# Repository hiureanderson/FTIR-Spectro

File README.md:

# FTIR-Spectro

A DIY Infrared spectrometry project based on michelson interferometry and Fourrier transform analysis
The system relies on a Atmega32u4 MCU as its core and the code is developed using the abstracted Arduino environment.

## What is the current state ?

Last Update: 27.08.2016
The FTIR DIY spectrometer is currently in stanbye and needs students for the project to continue on.
The project is currently based at Octanis Assocation, in the Hackuarium Hackerspace in Renens, Switzerland.
More can be found on these organisations at:

  http://octanis.org   
  http://wiki.hackuarium.ch/w/Main_Page
  
## What needs to be done ?

* Change CAD so that material swelling due to water uptake is taken into account (or change Nylon for a more stable material)
* Retest the stability of the AC-DC network 96V rectifier down to mV oscillations
* Make a proper PCB board for the 96V rectifier with BOM and dedicated documentation and Specs
* Align the mirrors system with a laser
* Test the mirror displacement due to the piezo crystal with a laser and charaterize it
* Program the Atmega MCU to drive the DAC output and test this output voltage (it might be necessary to reorder a board)
* Couple the Atmega MCU to the 0-5V --> 0-96V converter and charaterize the output voltage
* Test the Control of the piezo dilatation with the Atmega and the 0-96V output you charaterized
* Determine if the sensor sensitivity is high enough, if not various options can be explored: change the amplifier resistor bridge, cool the sensor down to -50°C with a Peltier dedicated device to reduce SNR, test a PIR type of sensor, find a more suited sensor.
* Once this stage is complete determine how much light is lost passing in the PE liquid holding cell when empty and scan with the piezo to get the empty cell response (need to program a control loop on the MCU with sensor reading)
* Test the device with different liquids and perform fft on the data provided by the Atmega board to get spectra
* Charaterize for ammonia detection
* Provide a deliverable kit with user manual

Each step must be documented so no work is lost and the community can enjoy the results !!

## Contact

You can contact me concerning the project at quentin.cabrol@gmail.com.
We are currently searching for members to enroll and work on this project

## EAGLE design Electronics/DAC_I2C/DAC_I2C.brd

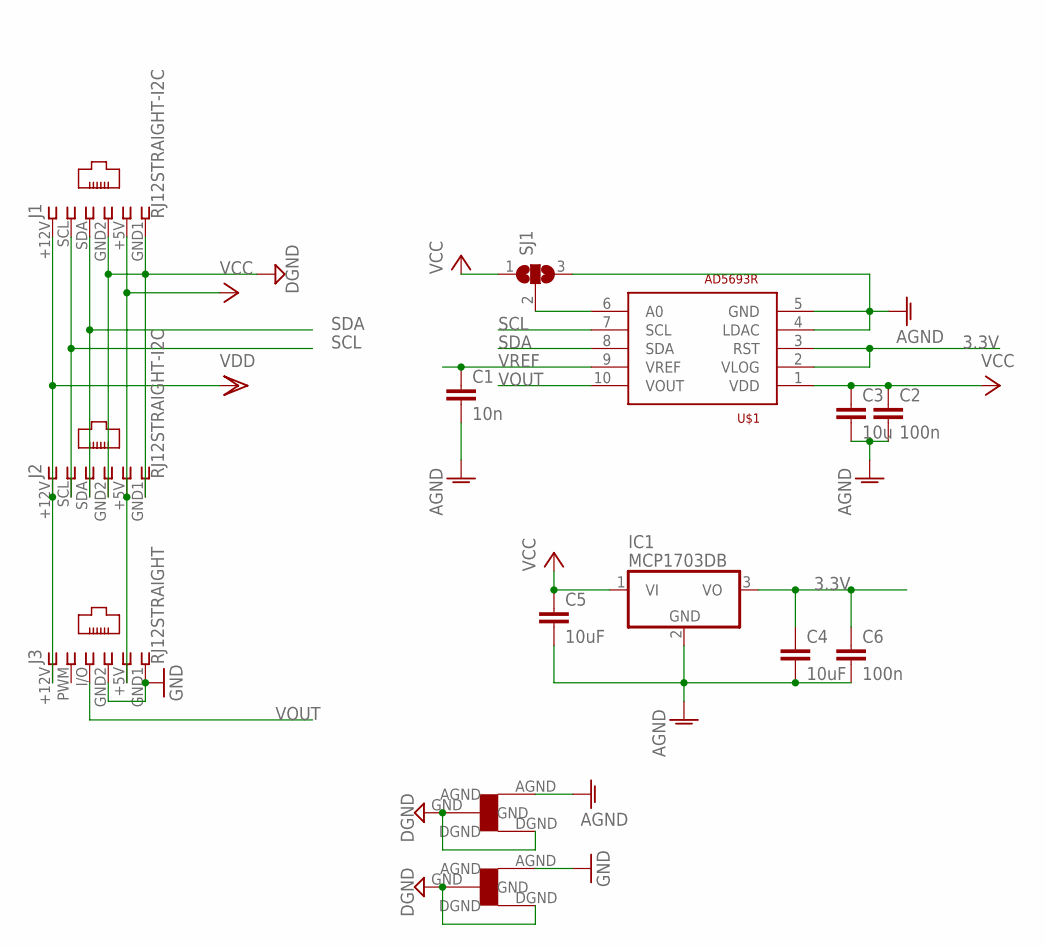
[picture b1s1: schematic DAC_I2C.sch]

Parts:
C1: 10n; C1206
C2, C6: 100n; C1206
C3: 10u; C1206
C4, C5: 10uF; C1206
IC1: MCP1703DB; SOT223
J1, J2: RJ12STRAIGHT-I2C; RJ12-STRAIGHT-I2C
J3: RJ12STRAIGHT; RJ12-STRAIGHT
SJ1: SJ2W; SJ_2
U$1: AD5693R; MSOP10
U$2, U$5: STARGND; STAR

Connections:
3.3V: C4.1, C6.1, IC1.3 (VO), U$1.2 (VLOG), U$1.3 (RST)
AGND: C1.2, C2.2, C3.2, C4.2, C5.2, C6.2, IC1.2 (GND), SJ1.3, U$1.4 (LDAC), U$1.5 (GND), U$5.AGND
DGND: J1.GND1 (6), J1.GND2 (4), J2.GND1 (6), J2.GND2 (4), U$2.DGND, U$2.GND, U$5.DGND, U$5.GND
GND: J3.GND1 (6), J3.GND2 (4), U$2.AGND
unnamed: SJ1.2, U$1.6 (A0)
SCL: J1.SCL (2), J2.SCL (2), U$1.7 (SCL)
SDA: J1.SDA (3), J2.SDA (3), U$1.8 (SDA)
VCC: C2.1, C3.1, C5.1, IC1.1 (VI), J1.+5V (5), J2.+5V (5), J3.+5V (5), SJ1.1, U$1.1 (VDD)
VDD: J1.+12V (1), J2.+12V (1), J3.+12V (1)
VOUT: J3.I/O (3), U$1.10 (VOUT)
VREF: C1.1, U$1.9 (VREF)

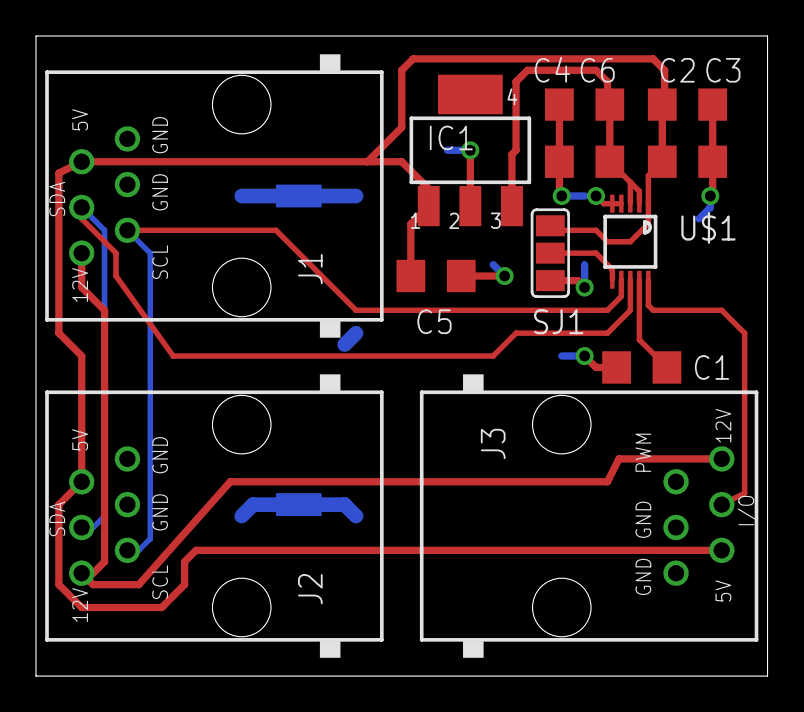
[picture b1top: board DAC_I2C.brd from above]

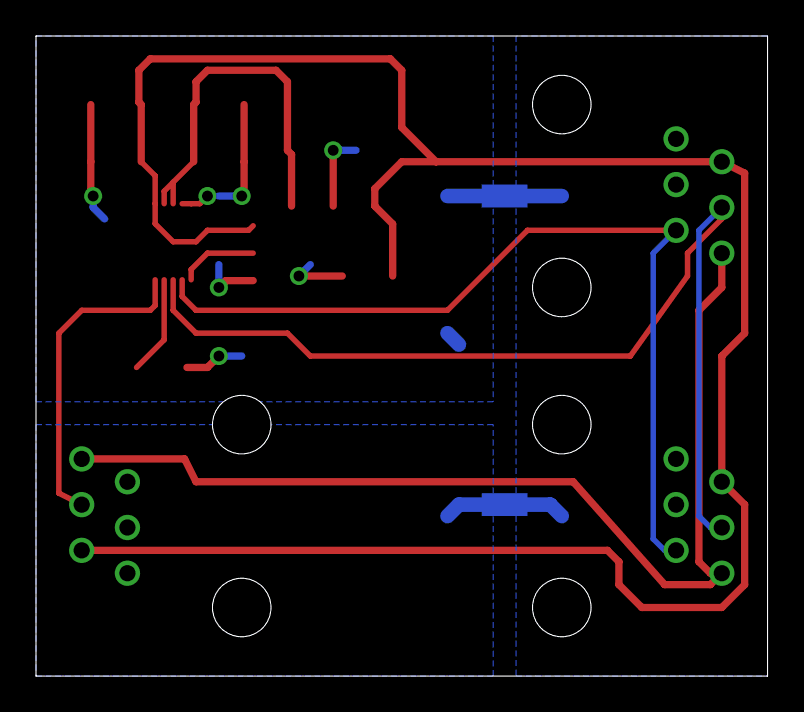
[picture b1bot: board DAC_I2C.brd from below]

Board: 2 copper layers, 40.6 x 35.6 mm, 14 parts (2 on the bottom side), 11 nets.

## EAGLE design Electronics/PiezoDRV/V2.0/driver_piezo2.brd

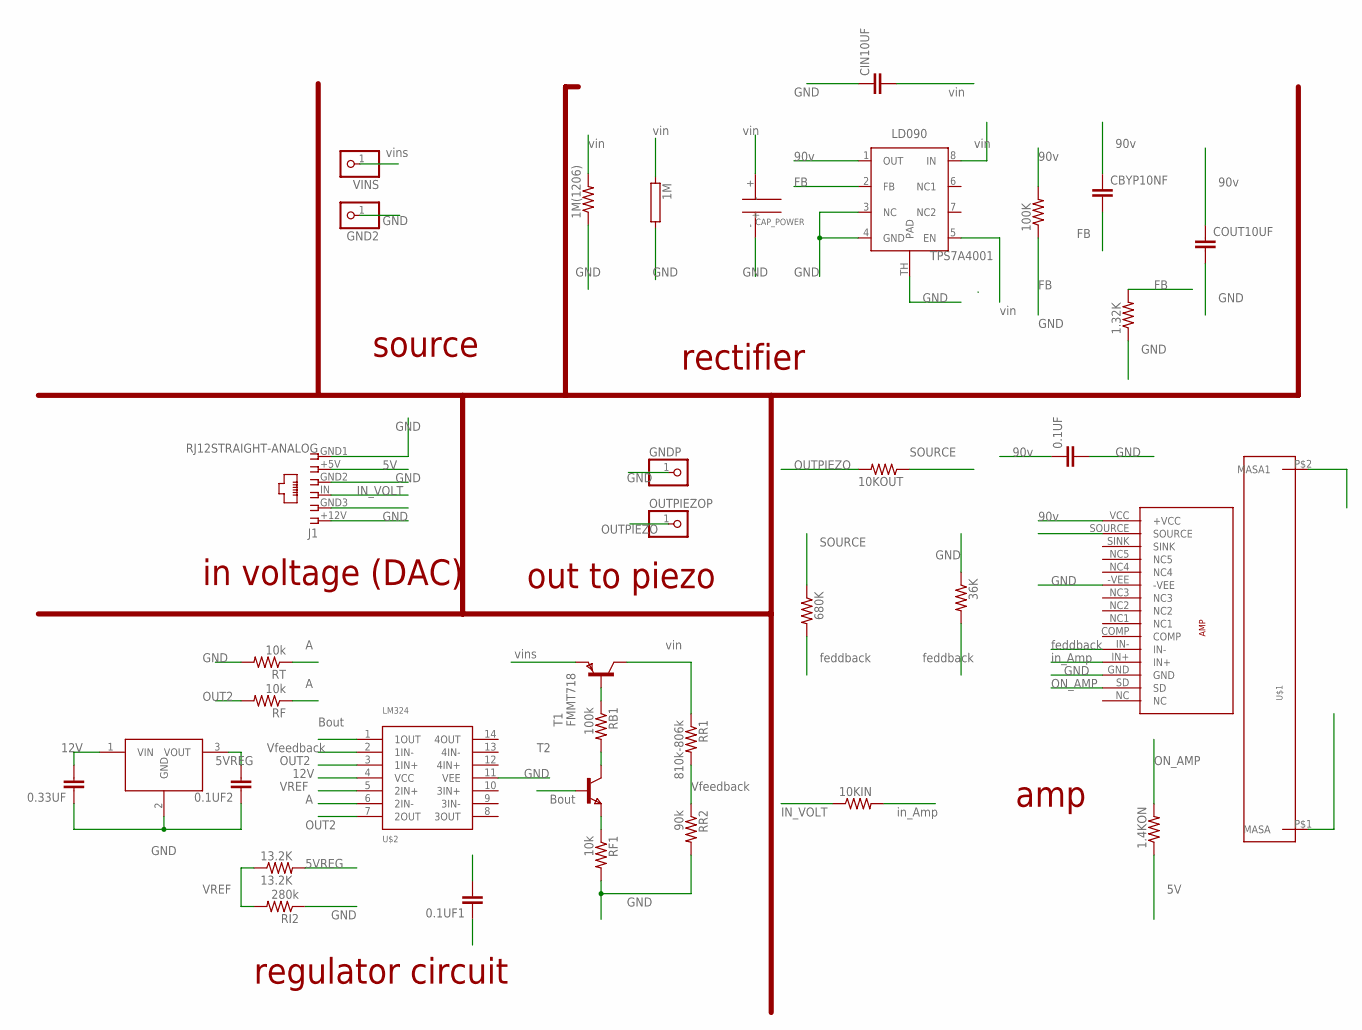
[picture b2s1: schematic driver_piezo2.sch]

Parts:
0.1UF, 0.1UF1, 0.1UF2, 0.33UF: C-EUC1206; C1206
1.4KON, 1.32K, 1M(1206), 10KIN, 10KOUT, 36K, 100K, 680K: R-US_R1206; R1206
1M: RCA0002; CA0002
13.2K: 13.2K; R1206
AMP: POWER_AMP_LME49811TB
CAP_POWER: CAP200VCAP200V; CAP200V
CBYP10NF: C-EUC1206; C1206
CIN10UF: C-EUC1206; C1206
COUT10UF: C-EUC1206; C1206
GND2: PINHD-1X1; 1X01
GNDP: PINHD-1X1; 1X01
J1: RJ12STRAIGHT-ANALOG; RJ12-STRAIGHT-ANALOG
LD090: TPS7A4001; S-PDSO-G08
OUTPIEZOP: PINHD-1X1; 1X01
RB1: 100k; R1206
RF, RF1: 10k; R1206
RI2: 280k; R1206
RR1: 810k-806k; R1206
RR2: 90k; R1206
RT: 10k; R1206
T1: FMMT718; SOT-23
T2: NPNSOT89; SOT89
U$1: DISIPADOR
U$2: LM324; SO14
U$3: 7805; TO220
VINS: PINHD-1X1; 1X01

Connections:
1OUT: T2.1 (B), U$2.1 (1OUT)
2IN+: 13.2K.1, RI2.2, U$2.5 (2IN+)
2IN-: RF.1, RT.1, U$2.6 (2IN-)
2OUT: RF.2, U$2.3 (1IN+), U$2.7 (2OUT)
5V: 1.4KON.1, J1.+5V (5)
5VOP: 0.1UF2.2, 13.2K.2, U$3.3 (VOUT)
12V: 0.1UF1.2, 0.33UF.2, J1.+12V (1), U$2.4 (VCC), U$3.1 (VIN)
B: 36K.2, 680K.2, AMP.IN-
FB: 1.32K.2, 100K.1, CBYP10NF.2, LD090.2 (FB)
GND: 0.1UF.2, 0.1UF1.1, 0.1UF2.1, 0.33UF.1, 1.32K.1, 1M.2, 1M(1206).1, 36K.1, AMP.-VEE, AMP.GND, CAP_POWER.-, CIN10UF.1, COUT10UF.2, GND2.1, GNDP.1, J1.GND1 (6), J1.GND2 (4), J1.GND3 (2), LD090.3 (NC), LD090.4 (GND), LD090.TH (PAD), RF1.2, RI2.1, RR2.2, RT.2, U$1.P$1 (MASA), U$1.P$2 (MASA1), U$2.11 (VEE), U$3.2 (GND)
IN_AMP: 10KIN.2, AMP.IN+
IN_VOLTAGE: 10KIN.1, J1.IN (3)
unnamed: RB1.2, T2.2 (C), T2.2@1 (C)
unnamed: RB1.1, T1.3 (B)
unnamed: RF1.1, T2.3 (E)
ON: 1.4KON.2, AMP.SD
OUT_PIEZO: 10KOUT.2, OUTPIEZOP.1
SOURCE: 10KOUT.1, 680K.1, AMP.SOURCE
V90: 0.1UF.1, 100K.2, AMP.VCC (+VCC), CBYP10NF.1, COUT10UF.1, LD090.1 (OUT)
VF: RR1.2, RR2.1, U$2.2 (1IN-)
VIN: 1M.1, 1M(1206).2, CAP_POWER.+, CIN10UF.2, LD090.5 (EN), LD090.8 (IN), RR1.1, T1.1 (C)
VINS: T1.2 (E), VINS.1

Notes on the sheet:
source
rectifier
out to piezo
amp
vins
vin
90v
GND
OUTPIEZO
IN_VOLT
ON_AMP
feddback
in voltage (DAC)
in_Amp
SOURCE
regulator circuit
Vfeedback
Bout
OUT2
12V
VREF
5VREG

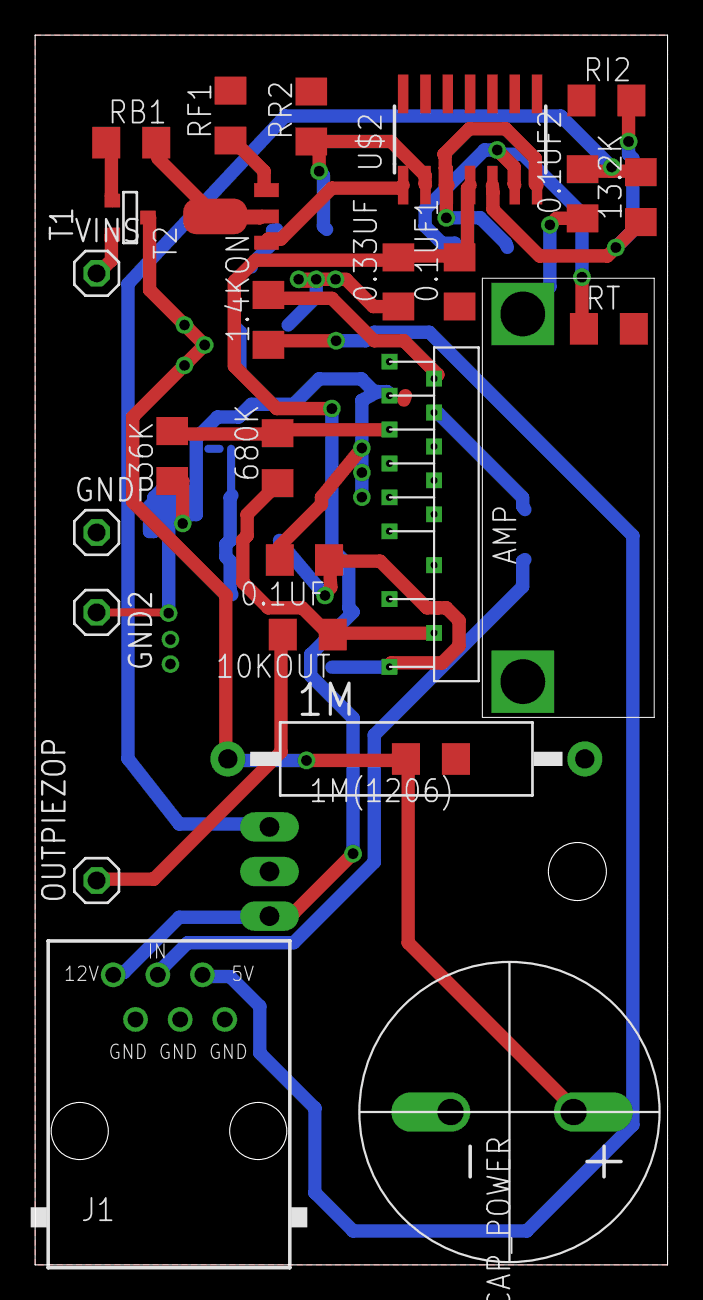
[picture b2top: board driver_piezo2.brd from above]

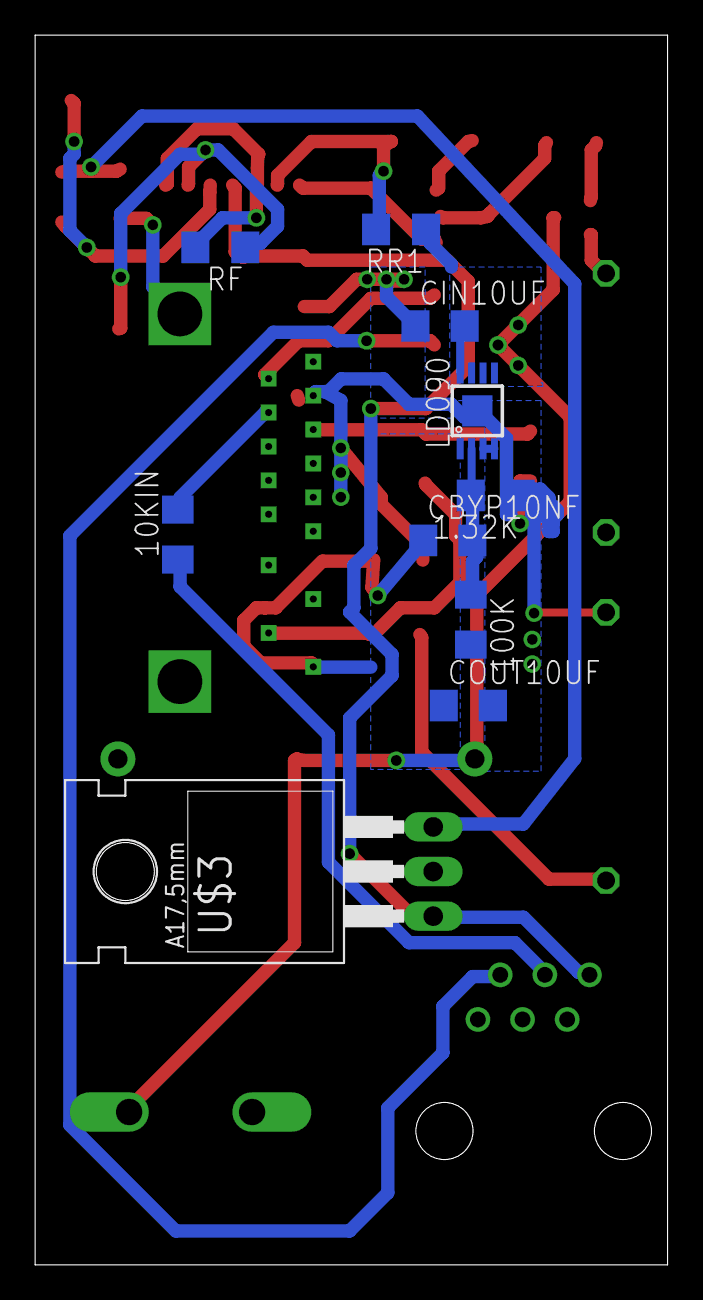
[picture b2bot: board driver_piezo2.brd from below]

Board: 2 copper layers, 36.0 x 70.0 mm, 37 parts (10 on the bottom side), 22 nets.

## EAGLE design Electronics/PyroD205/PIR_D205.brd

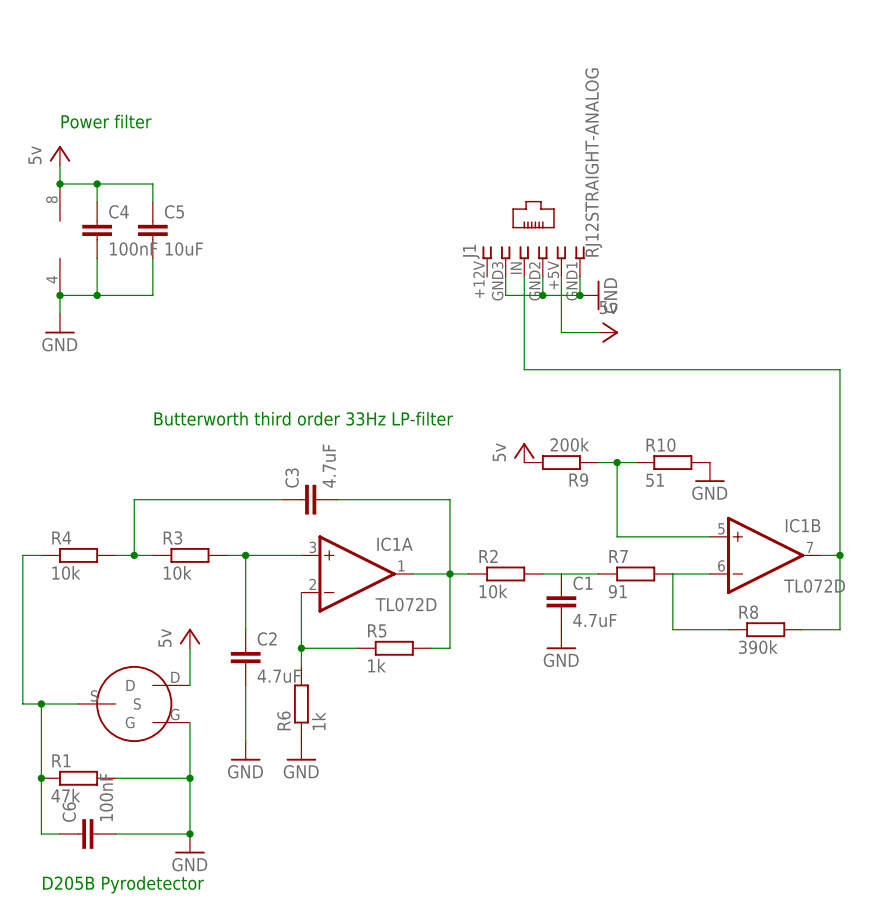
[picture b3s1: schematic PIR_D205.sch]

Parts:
C1, C2, C3: 4.7uF; C1206
C4, C6: 100nF; C1206
C5: 10uF; C1206
IC1: TL072D; SO08
J1: RJ12STRAIGHT-ANALOG; RJ12-STRAIGHT-ANALOG
R1: 47k; R1206
R2, R3, R4: 10k; R0805
R5, R6: 1k; R0805
R7: 91; R1206
R8: 390k; R1206
R9: 200k; R1206
R10: 51; R1206
U$1: D205B; TO5

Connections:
GND: C1.2, C2.2, C4.2, C5.2, C6.2, IC1.4 (V-), J1.GND1 (6), J1.GND2 (4), J1.GND3 (2), R1.2, R6.1, R10.2, U$1.G
unnamed: C6.1, R1.1, R4.1, U$1.S
unnamed: C3.2, IC1.1 (OUT), R2.1, R5.2
unnamed: IC1.2 (-IN), R5.1, R6.2
unnamed: C1.1, R2.2, R7.1
unnamed: C2.1, IC1.3 (+IN), R3.2
unnamed: C3.1, R3.1, R4.2
unnamed: IC1.6 (-IN), R7.2, R8.1
unnamed: IC1.7 (OUT), J1.IN (3), R8.2
unnamed: IC1.5 (+IN), R9.1, R10.1
VCC: C4.1, C5.1, IC1.8 (V+), J1.+5V (5), R9.2, U$1.D

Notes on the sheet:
Butterworth third order 33Hz LP-filter
D205B Pyrodetector
Power filter

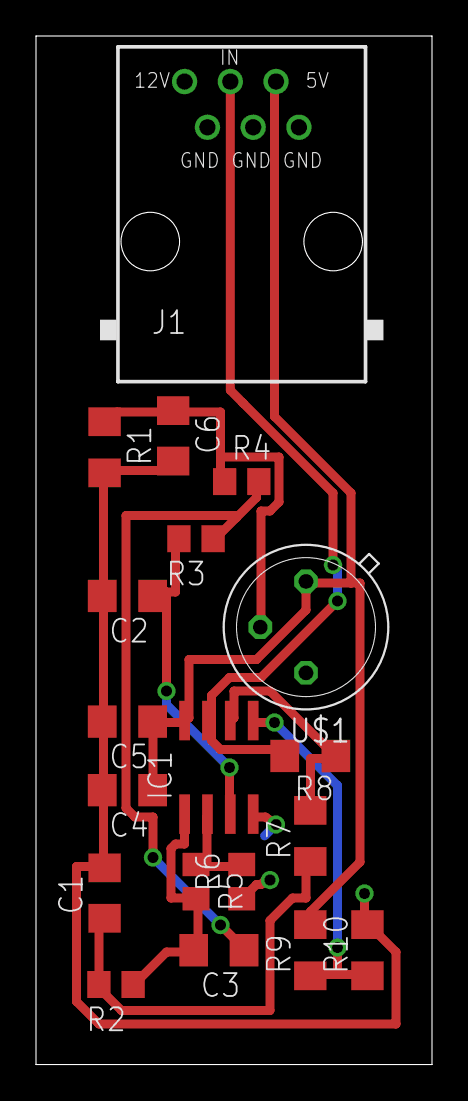
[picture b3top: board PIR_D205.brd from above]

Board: 2 copper layers, 22.0 x 57.1 mm, 19 parts (0 on the bottom side), 11 nets.

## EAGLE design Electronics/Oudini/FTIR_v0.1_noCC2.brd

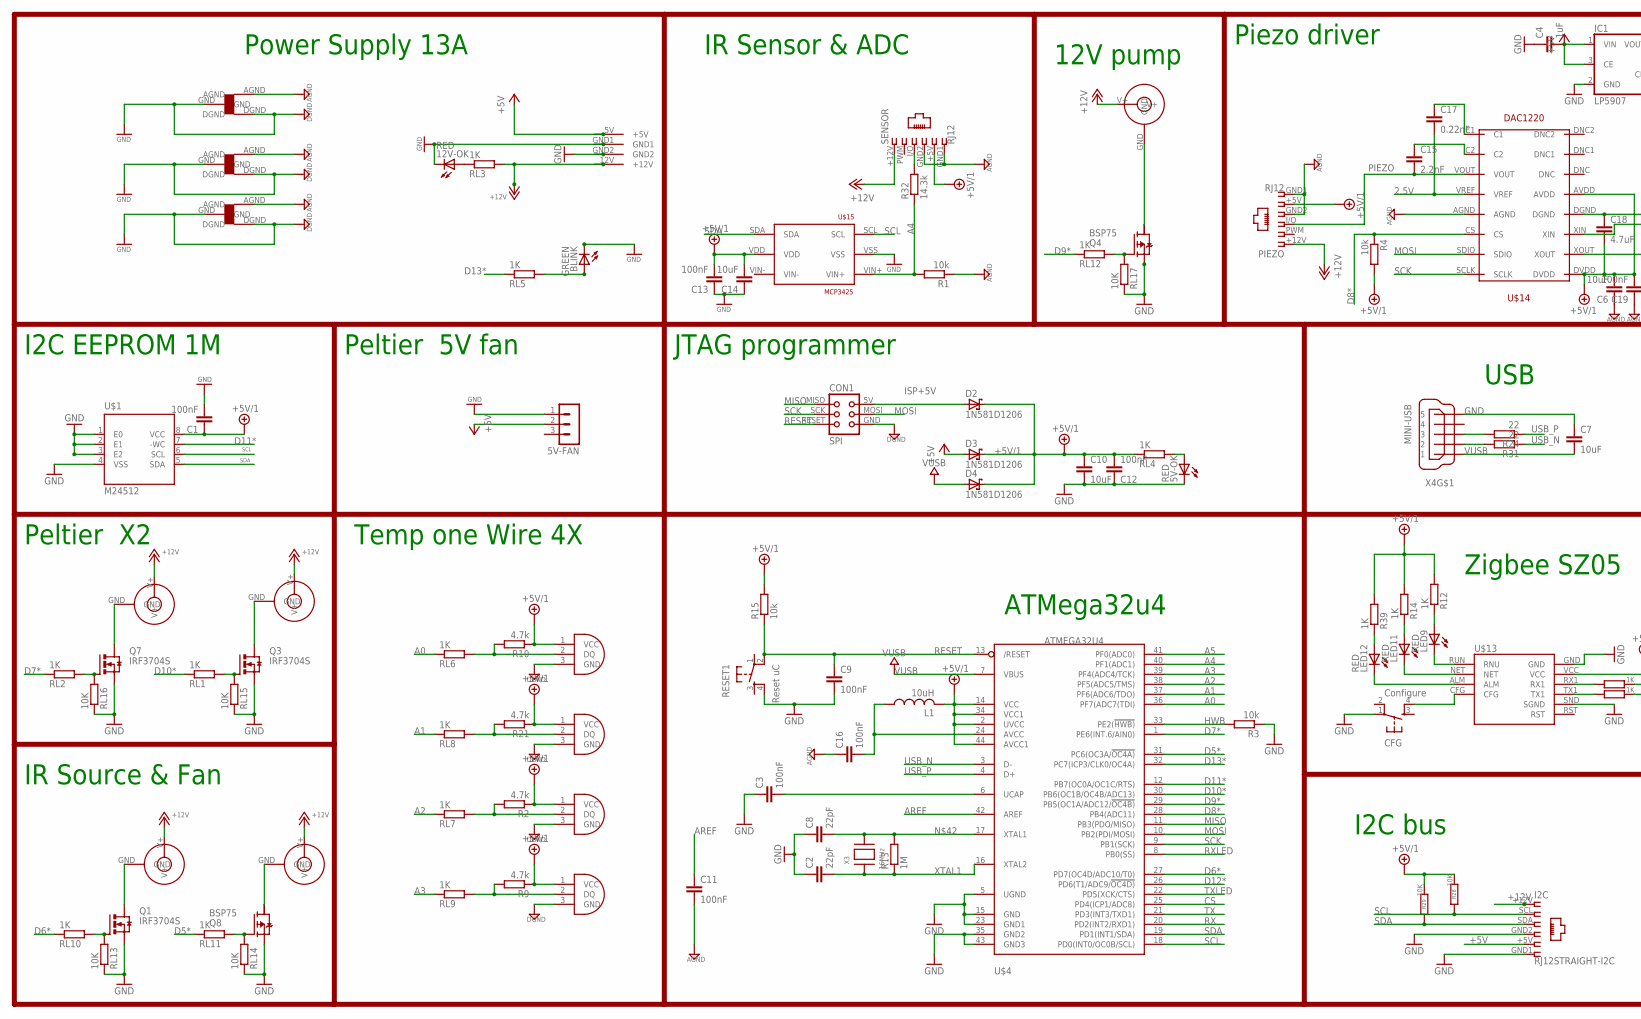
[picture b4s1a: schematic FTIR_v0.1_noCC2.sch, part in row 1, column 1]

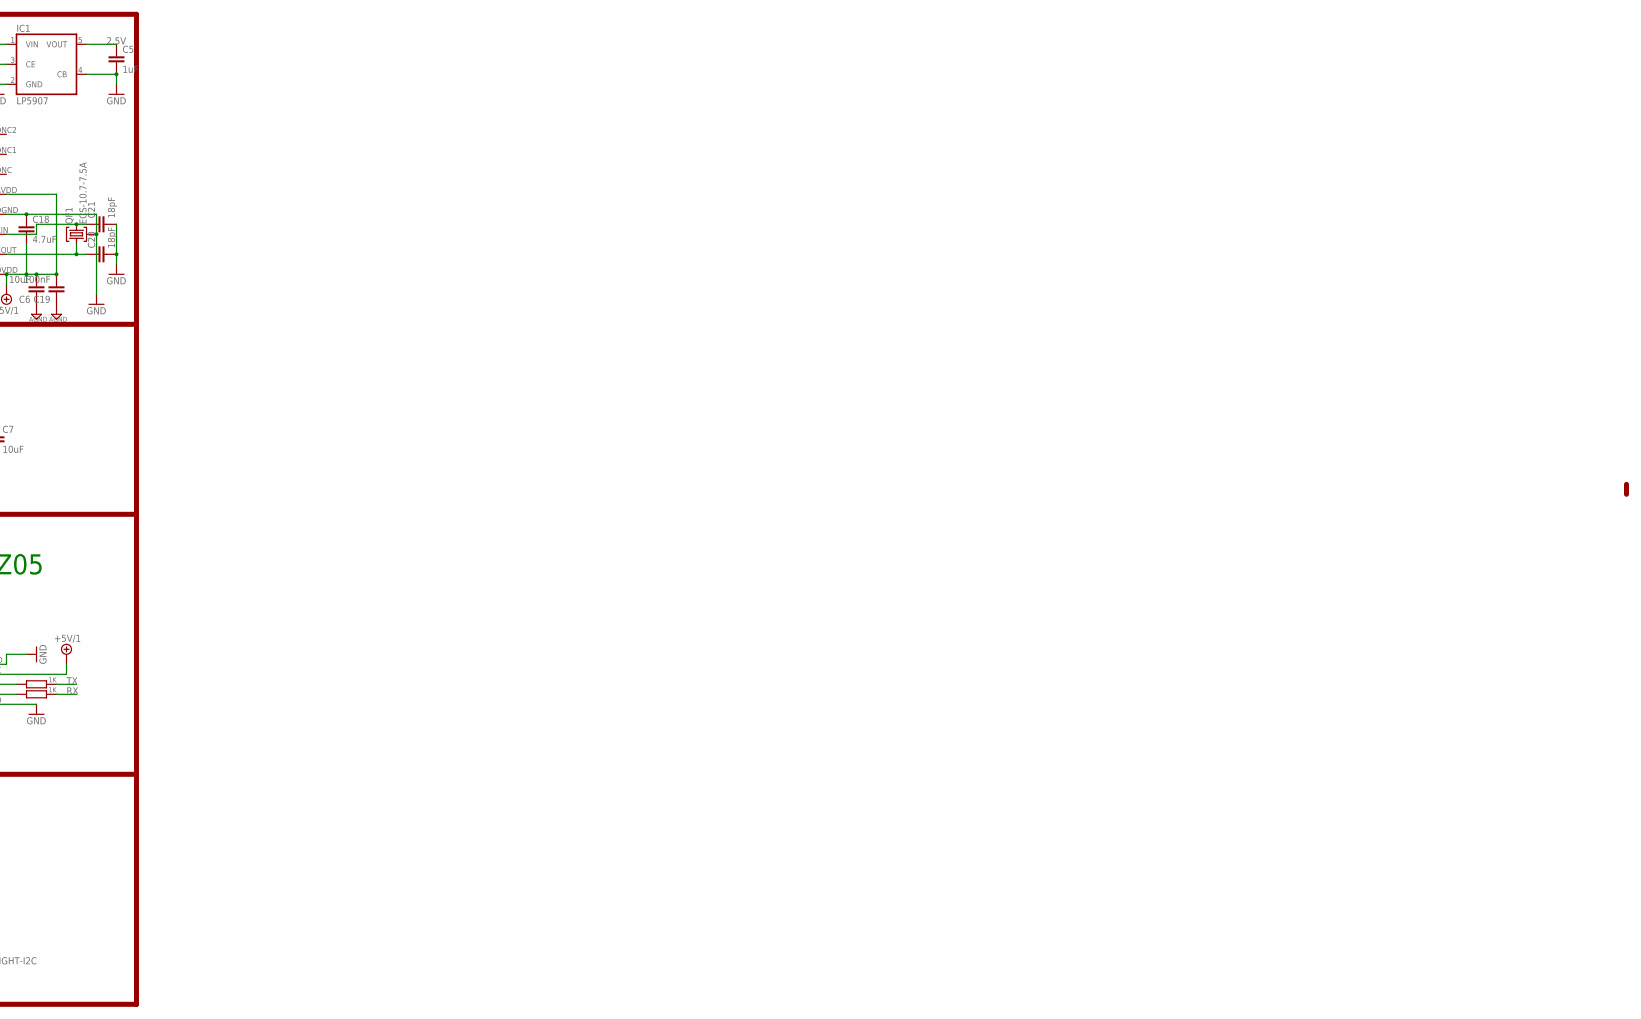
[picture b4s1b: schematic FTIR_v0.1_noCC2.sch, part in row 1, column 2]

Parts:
5V-FAN: MA03-1
5V-OK, 12V-OK: RED; CHIPLED_1206
BLINK: GREEN; CHIPLED_1206
C1, C3, C9, C11, C12, C13, C16, C19: 100nF; C1206
C2, C8: 22pF; C1206
C4, C5: 1uF; C1206
C6, C7, C10, C14: 10uF; C1206
C15: 2.2nF; C1206
C17: 0.22nF; C1206
C18: 4.7uF; C1206
C20, C21: 18pF; C1206
CFG: Configure; TACTILE_SWITCH_SMD
CON1: SPI; TC2030-MCP-NL
D2, D3, D4: 1N581D1206; LED-1206
I2C: RJ12STRAIGHT-I2C; RJ12-STRAIGHT-I2C
IC1: LP5907; SOT25
L1: 10uH; L2012C
LED9, LED11, LED12: RED; CHIPLED_1206
PIEZO: RJ12; RJ12-STRAIGHT
Q1, Q3, Q7: IRF3704S; D2PACK
Q4, Q8: BSP75; PG-SOT-223
QF1: ECS-10.7-7.5A; HC49U
R1, R4: 10k; R0805
R2, R9, R10, R21: 4.7k; R1206
R3, R15: 10k; M0805
R8, R11, R12, R14, R39: 1K; R0805
R13: 1M; R1206
R24, R31: 22; M1206
R28, R29: 10K; M0805
R32: 14.3k; R0805
RESET1: Reset uC; TACTILE_SWITCH_SMD
RL1, RL2, RL3, RL4, RL5, RL6, RL7, RL8, RL9, RL10, RL11, RL12: 1K; R0805
RL13, RL14, RL15, RL16, RL17: 10K; R0805
SENSOR: RJ12; RJ12-STRAIGHT
U$1: M24512; SO8
U$2, U$5, U$20: STARGND; STAR
U$3: AMP_MATE_N_LOCK
U$4: ATMEGA32U4; TQFP44
U$6, U$16, U$17, U$18, U$19: JACK_PJ-063BH; PJ-063BH
U$9, U$10, U$11, U$12: DS18B20_PINS; 3PINS_SMALL
U$13: SZ05-ZIGBEESMD; SZ05-ZIGBEE3
U$14: DAC1220; SSOP-16
U$15: MCP3425; SOT-23-6
X3: 16MHz; NX6035
X4: MINI-USB; 32005-201

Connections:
2.5V: C5.1, C17.2, IC1.5 (VOUT), U$14.VREF
+5V: 5V-FAN.2, C4.2, D3.A, I2C.+5V (5), IC1.1 (VIN), IC1.3 (CE), U$3.5V (+5V)
+5V/1: C1.1, C6.2, C10.1, C12.2, C13.2, C14.2, C18.2, C19.2, D2.C, D3.C, D4.C, L1.2, PIEZO.+5V (5), R2.1, R4.2, R9.1, R10.1, R12.2, R14.2, R15.2, R21.1, R28.1, R29.1, R39.2, RL4.1, SENSOR.+5V (5), U$1.8 (VCC), U$4.2 (UVCC), U$4.14 (VCC), U$4.34 (VCC1), U$4.44 (AVCC1), U$9.1 (VCC), U$10.1 (VCC), U$11.1 (VCC), U$12.1 (VCC), U$13.VCC, U$14.AVDD, U$14.DVDD, U$15.VDD
+12V: I2C.+12V (1), PIEZO.+12V (1), RL3.2, SENSOR.+12V (1), U$3.12V (+12V), U$6.V+, U$16.V+, U$17.V+, U$18.V+, U$19.V+
A0: RL6.1, U$4.36 (PF7(ADC7(TDI))
A1: RL8.1, U$4.37 (PF6(ADC6/TDO))
A2: RL7.1, U$4.38 (PF5(ADC5/TMS))
A3: RL9.1, U$4.39 (PF4(ADC4/TCK))
A4: R1.2, R32.1, U$4.40 (PF1(ADC1)), U$15.VIN+
A5: U$4.41 (PF0(ADC0))
AGND: C6.1, C11.2, C16.1, C19.1, PIEZO.GND1 (6), PIEZO.GND2 (4), R1.1, SENSOR.GND1 (6), SENSOR.GND2 (4), U$2.AGND, U$5.AGND, U$14.AGND, U$20.AGND
AREF: C11.1, U$4.42 (AREF)
CS: U$4.25 (PD4(ICP1/ADC8))
D5*: RL11.1, U$4.31 (PC6(OC3A/!OC4A))
D6*: RL10.1, U$4.27 (PD7(OC4D/ADC10/T0))
D7*: RL2.1, U$4.1 (PE6(INT.6/AIN0))
D8*: R4.1, U$4.28 (PB4(ADC11)), U$14.CS
D9*: RL12.1, U$4.29 (PB5(OC1A/ADC12/!OC4B))
D10*: RL1.1, U$4.30 (PB6(OC1B/OC4B/ADC13))
D11*: U$1.7 (-WC), U$4.12 (PB7(OC0A/OC1C/RTS))
D12*: U$4.26 (PD6(T1/ADC9/!OC4D))
D13*: RL5.1, U$4.32 (PC7(ICP3/CLK0/OC4A))
GND: 5V-FAN.1, 5V-OK.C, 12V-OK.C, BLINK.C, C1.2, C2.1, C3.1, C4.1, C5.2, C7.1, C8.1, C9.2, C10.2, C12.1, C13.1, C14.1, C18.1, C20.2, C21.2, CFG.1, CON1.GND, I2C.GND1 (6), I2C.GND2 (4), IC1.2 (GND), IC1.4 (CB), Q1.3 (S), Q3.3 (S), Q4.3 (S), Q7.3 (S), Q8.3 (S), QF1.2, R3.1, RESET1.4, RL13.1, RL14.1, RL15.1, RL16.1, RL17.1, U$1.1 (E0), U$1.2 (E1), U$1.3 (E2), U$1.4 (VSS), U$2.DGND, U$2.GND, U$3.GND1, U$3.GND2, U$4.5 (UGND), U$4.15 (GND), U$4.23 (GND1), U$4.35 (GND2), U$4.43 (GND3), U$5.DGND, U$5.GND, U$9.3 (GND), U$10.3 (GND), U$11.3 (GND), U$12.3 (GND), U$13.GND, U$13.SND (SGND), U$14.DGND, U$15.VSS, U$20.DGND, U$20.GND, X4.5
GND1: LED9.C, U$13.RUN (RNU)
GND2: LED11.C, U$13.NET
GND3: LED12.C, U$13.ALM
HWB: R3.2, U$4.33 (PE2(!HWB))
ISP+5V: CON1.5V (VCC), D2.A
MISO: CON1.MISO, U$4.11 (PB3(PDO/MISO))
MOSI: CON1.MOSI, U$4.10 (PB2(PDI/MOSI)), U$14.SDIO
unnamed: Q4.1 (G), RL12.2, RL17.2
unnamed: R32.2, SENSOR.I/O (3)
unnamed: BLINK.A, RL5.2
unnamed: Q4.2 (D), U$19.GND
unnamed: Q7.1 (G), RL2.2, RL16.2
unnamed: Q1.2 (D), U$17.GND
unnamed: R21.2, RL8.2, U$10.2 (DQ)
unnamed: R11.2, U$13.RX1
unnamed: 5V-OK.A, RL4.2
unnamed: Q3.1 (G), RL1.2, RL15.2
unnamed: C16.2, L1.1, U$4.24 (AVCC)
unnamed: C15.1, U$14.C2
unnamed: C3.2, U$4.6 (UCAP)
unnamed: R2.2, RL7.2, U$11.2 (DQ)
unnamed: R9.2, RL9.2, U$12.2 (DQ)
unnamed: C21.1, QF1.3, U$14.XIN
unnamed: R10.2, RL6.2, U$9.2 (DQ)
unnamed: Q8.2 (D), U$18.GND
unnamed: R8.2, U$13.TX1
unnamed: LED9.A, R12.1
unnamed: LED11.A, R14.1
unnamed: LED12.A, R39.1
unnamed: Q1.1 (G), RL10.2, RL13.2
unnamed: C17.1, U$14.C1
unnamed: Q7.2 (D), U$6.GND
unnamed: C20.1, QF1.1, U$14.XOUT
unnamed: Q3.2 (D), U$16.GND
unnamed: CFG.4, U$13.CFG
unnamed: Q8.1 (G), RL11.2, RL14.2
unnamed: C8.2, R13.2, U$4.17 (XTAL1), X3.P$2
unnamed: 12V-OK.A, RL3.1
PIEZO: C15.2, PIEZO.I/O (3), U$14.VOUT
RESET: C9.1, CON1.RESET, R15.1, RESET1.2, U$4.13 (/RESET)
RX: R8.1, U$4.20 (PD2(INT2/RXD1))
RXLED: U$4.8 (PB0(SS))
SCK: CON1.SCK, U$4.9 (PB1(SCK)), U$14.SCLK
SCL: I2C.SCL (2), R28.2, U$1.6 (SCL), U$4.18 (PD0(INT0/OC0B/SCL)), U$15.SCL
SDA: I2C.SDA (3), R29.2, U$1.5 (SDA), U$4.19 (PD1(INT1/SDA)), U$15.SDA
TX: R11.1, U$4.21 (PD3(INT3/TXD1))
TXLED: U$4.22 (PD5(XCK/CTS))
USBC_N: R31.2, X4.2
USBC_P: R24.2, X4.3
USB_N: R31.1, U$4.3 (D-)
USB_P: R24.1, U$4.4 (D+)
VUSB: C7.2, D4.A, U$4.7 (VBUS), X4.1
XTAL1: C2.2, R13.1, U$4.16 (XTAL2), X3.P$1

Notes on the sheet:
I2C EEPROM 1M
ATMega32u4
USB
Power Supply 13A
Zigbee SZ05
Peltier X2
Temp one Wire 4X
I2C bus
JTAG programmer
Piezo driver
IR Source & Fan
IR Sensor & ADC
12V pump
Peltier 5V fan

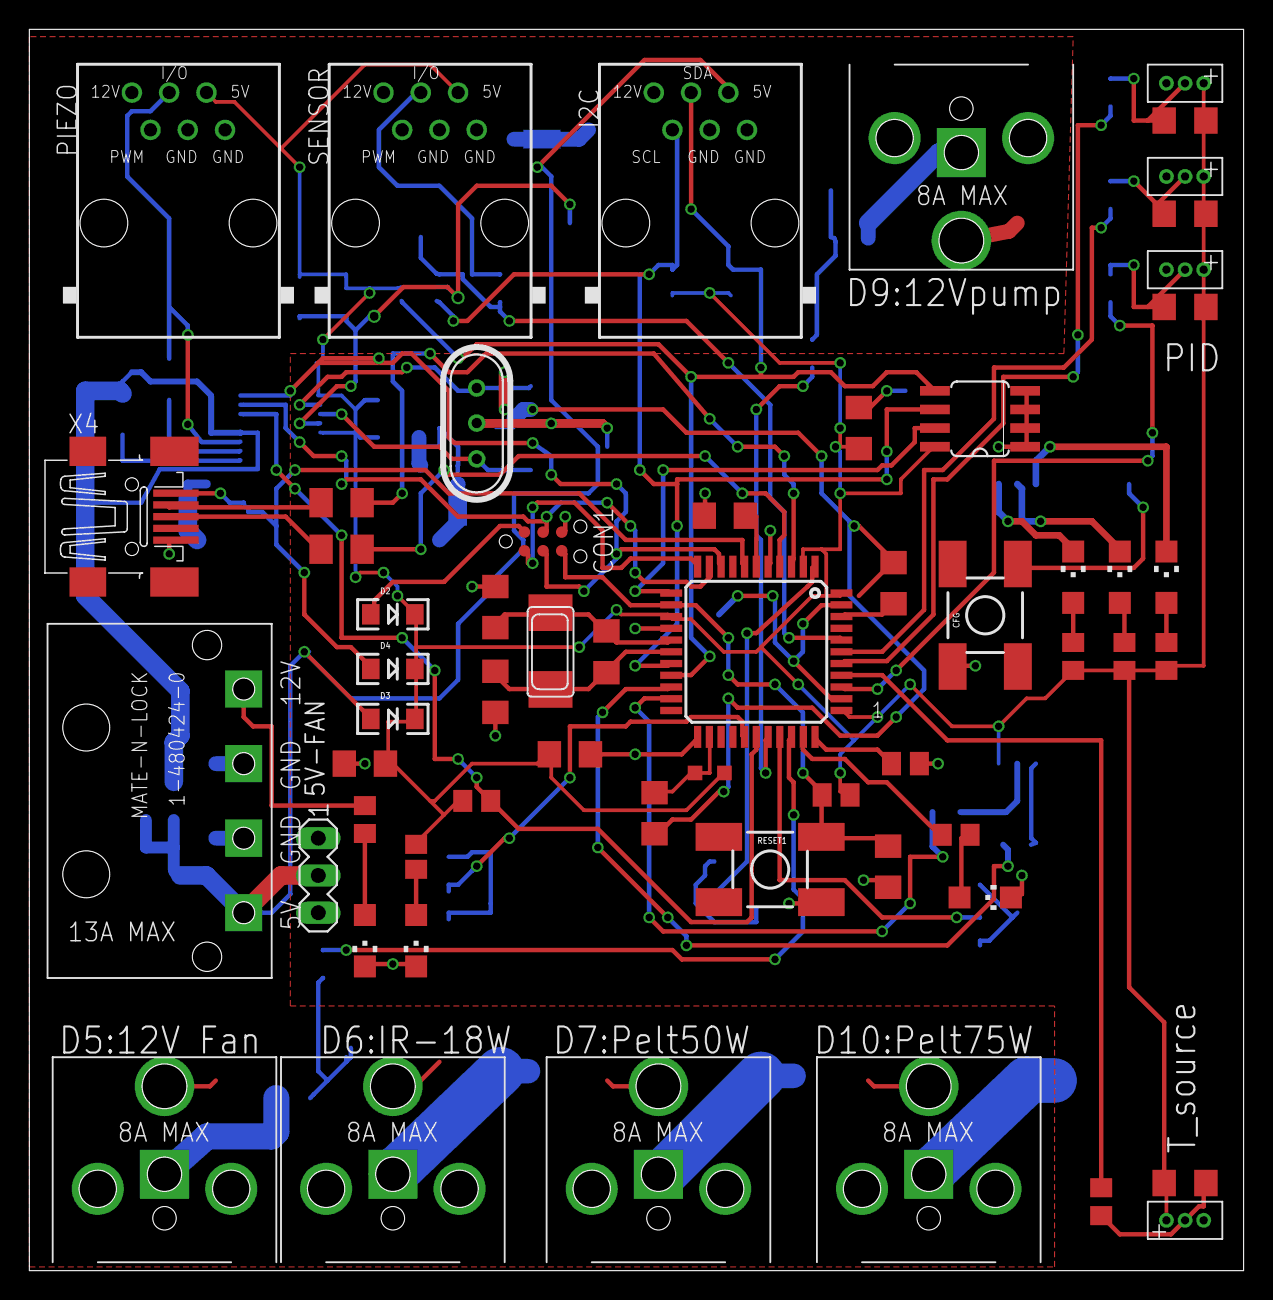
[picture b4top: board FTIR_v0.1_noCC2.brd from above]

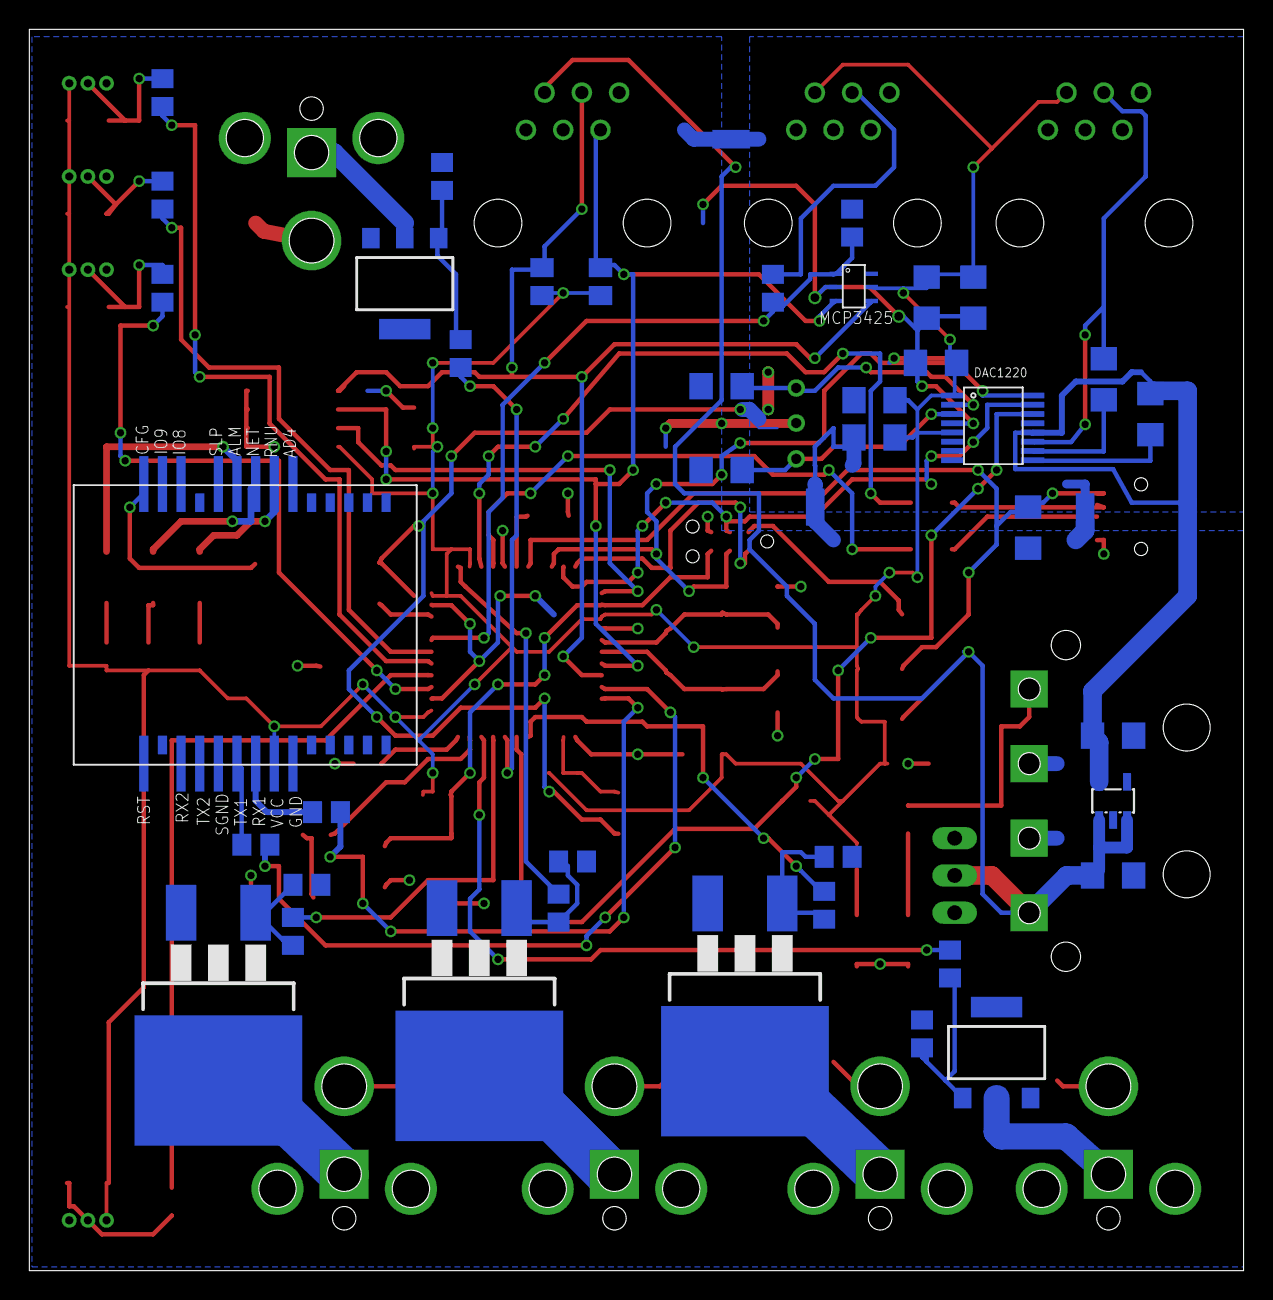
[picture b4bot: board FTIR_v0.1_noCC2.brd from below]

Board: 4 copper layers, 82.7 x 84.6 mm, 101 parts (43 on the bottom side), 71 nets.

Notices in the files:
parts and their libraries:
lpatiny: ©2009 ROFA.cz - modified and updated by Robert Darlington ‹rdarlington@gmail.com›
